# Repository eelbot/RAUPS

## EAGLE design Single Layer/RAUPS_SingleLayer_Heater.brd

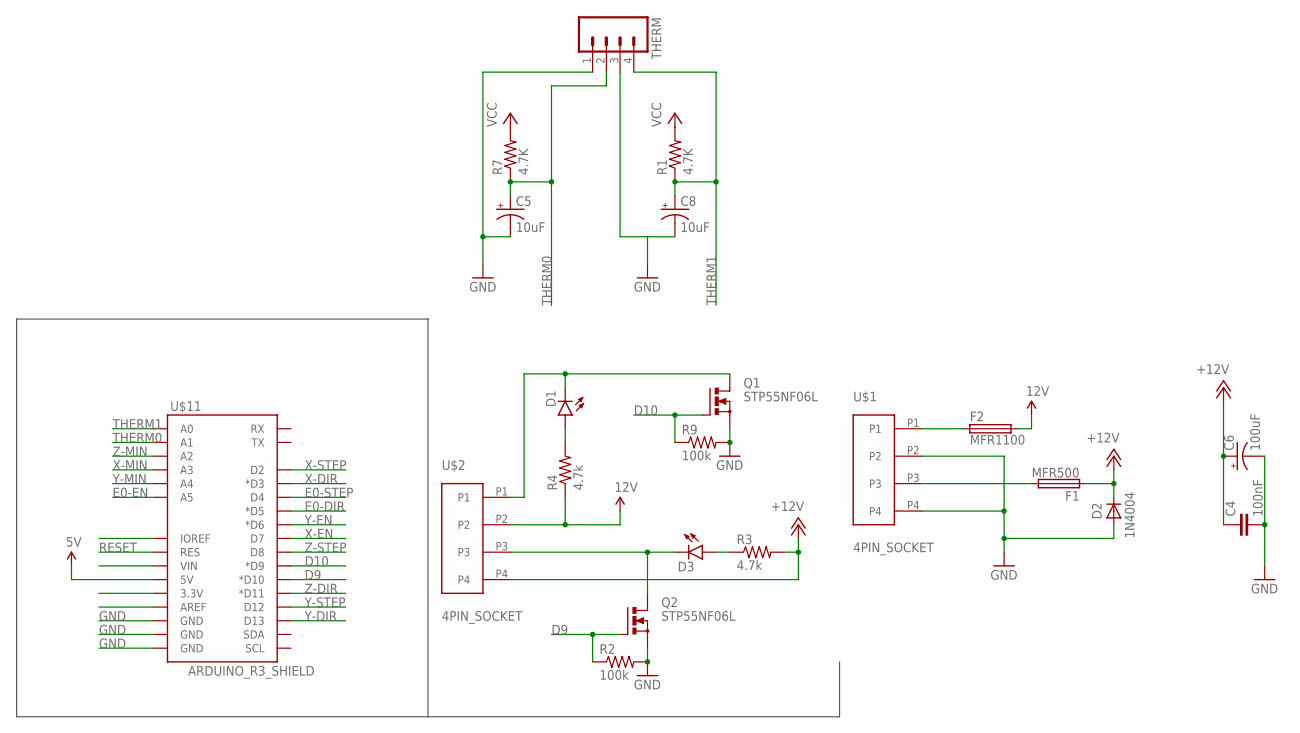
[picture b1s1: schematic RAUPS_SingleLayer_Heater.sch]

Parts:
C4: 100nF; C2.5-3
C5, C8: 10uF; E2,5-5
C6: 100uF; E3,5-8
D1, D3: LED-3MM-NO_SILK; LED3MM-NS
D2: 1N4004; DO41-10
F1: MFR500
F2: MFR1100
Q1, Q2: STP55NF06L; TO220BV
R1, R7: 4.7K; 0207/7
R2, R9: 100k; 0207/7
R3, R4: 4.7k; AXIAL-0.3
THERM: M04LONGPADS; 1X04_LONGPADS
U$1, U$2: 4PIN_SOCKET; CONN-4PIN
U$11: ARDUINO_R3_SHIELD; UNO_R3_SHIELD

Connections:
5V: U$11.5V
12V: F2.2, R4.P$1 (1), U$2.P2
+12V: C4.1, C6.+, D2.C, F1.1, R3.P$2 (2), U$2.P4
D9: Q2.G, R2.1, U$11.D10 (*D10)
D10: Q1.G, R9.1, U$11.D9 (*D9)
E0-DIR: U$11.D5 (*D5)
E0-EN: U$11.A5
E0-STEP: U$11.D4
GND: C4.2, C5.-, C6.-, C8.-, D2.A, Q1.S, Q2.S, R2.2, R9.2, THERM.1, THERM.3, U$1.P2, U$1.P4, U$11.GND@0 (GND), U$11.GND@1 (GND), U$11.GND@2 (GND)
unnamed: D3.K (C), Q2.D, U$2.P3
unnamed: F2.1, U$1.P1
unnamed: D1.K (C), Q1.D, U$2.P1
unnamed: F1.2, U$1.P3
unnamed: D1.A, R4.P$2 (2)
unnamed: D3.A, R3.P$1 (1)
RESET: U$11.RES
THERM0: C5.+, R7.1, THERM.2, U$11.A1
THERM1: C8.+, R1.1, THERM.4, U$11.A0
VCC: R1.2, R7.2
X-DIR: U$11.D3 (*D3)
X-EN: U$11.D7
X-MIN: U$11.A3
X-STEP: U$11.D2
Y-DIR: U$11.D13
Y-EN: U$11.D6 (*D6)
Y-MIN: U$11.A4
Y-STEP: U$11.D12
Z-DIR: U$11.D11 (*D11)
Z-MIN: U$11.A2
Z-STEP: U$11.D8

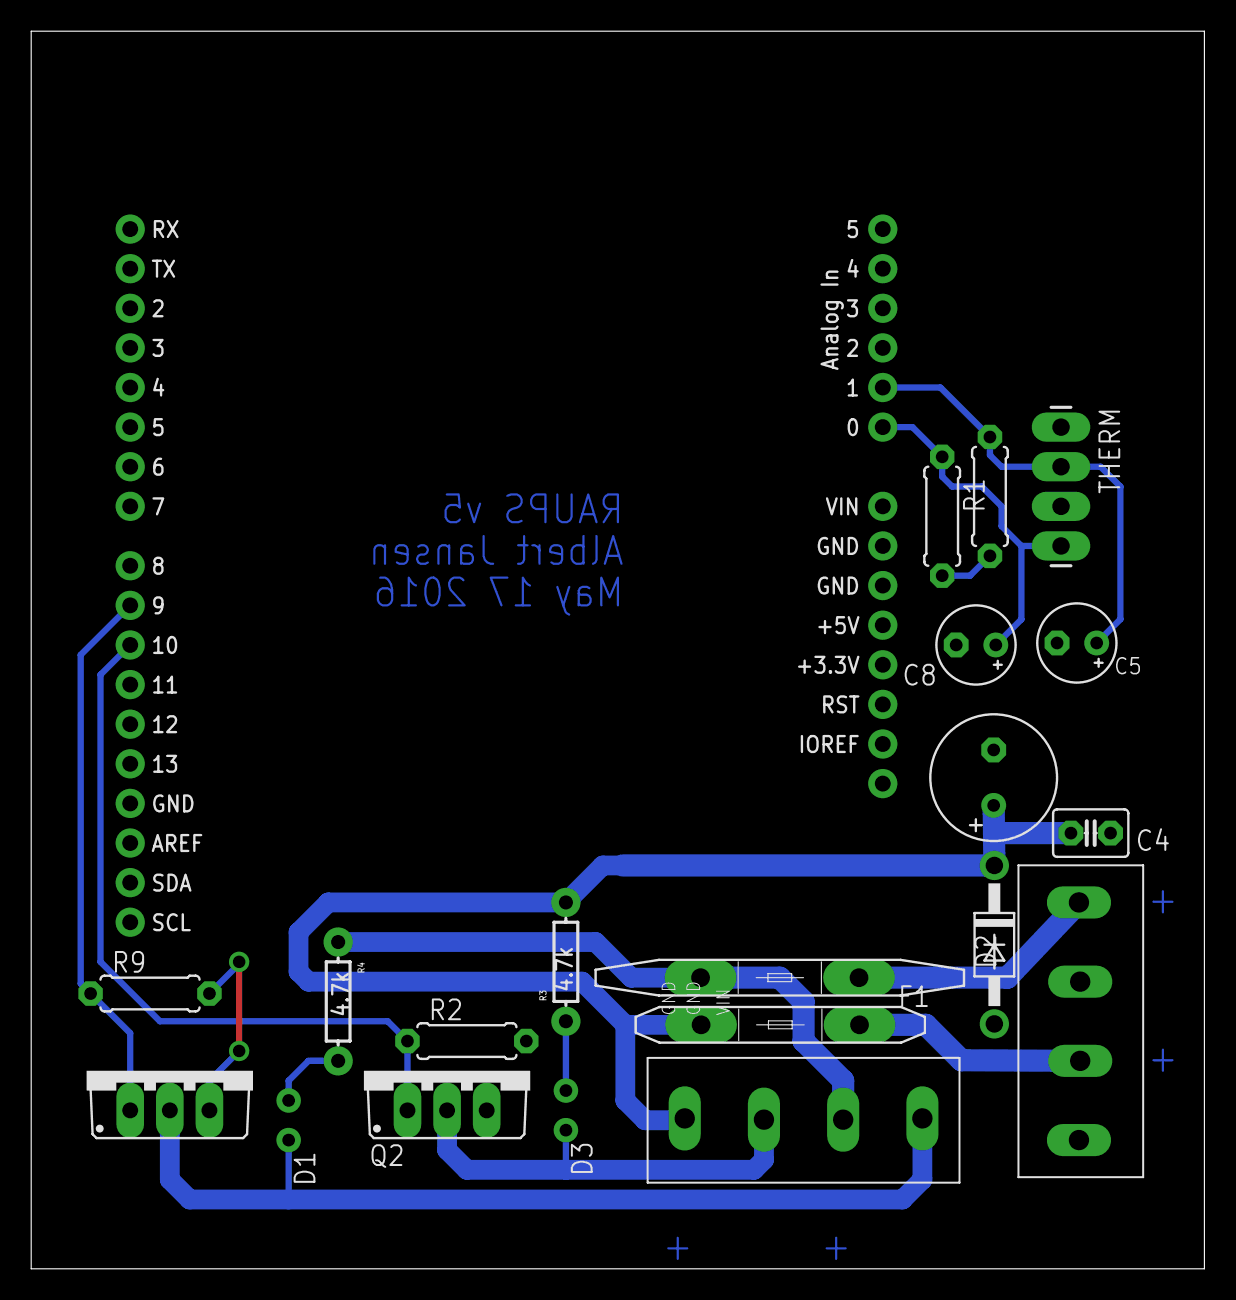
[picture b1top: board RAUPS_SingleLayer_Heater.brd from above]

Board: 2 copper layers, 75.2 x 79.4 mm, 21 parts (0 on the bottom side), 14 nets.

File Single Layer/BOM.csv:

Part Name,Package,Quantity,Digikey Part Number
Indicator LED,3mm,2,365-1173-ND
"1x3 0.1"" Header",PTH,3,3M9448-ND
"2x3 0.1"" Header",PTH,4,3M9459-ND
"1x4 0.1"" Header",PTH,6,3M9449-ND
"1x6 0.1"" Header",PTH,2,3M9451-ND
"1x8 0.1"" Header (Female)",PTH,8,S7041-ND
"1x8 0.1"" Header (Male)",PTH,4,3M9452-ND
"1x10 0.1"" Header",PTH,2,609-3250-ND
4.7k Resistor,PTH,2,S4.7KCACT-ND
10k Resistor,PTH,4,CF14JT10K0CT-ND
100k Resistor,PTH,6,CF14JT100KCT-ND
100nF Capacitor,PTH,2,445-5303-ND
100uF Capacitor,PTH,2,P5182-ND
10uF Capacitor,PTH,2,445-5339-ND
1N4004 Diode,PTH,2,1N4004FSCT-ND
"0.2"" Pitch Screw Terminal (2POS)",PTH,1,ED10561-ND
"0.2"" Pitch Screw Terminal (4POS)",PTH,1,ED10563-ND
PTC Resettable Fuse (11A),PTH,1,RGEF1100-ND
PTC Resettable Fuse (5A),PTH,2,MF-R500-ND
STP55NF06L MOSFET,PTH,2,497-6742-5-ND

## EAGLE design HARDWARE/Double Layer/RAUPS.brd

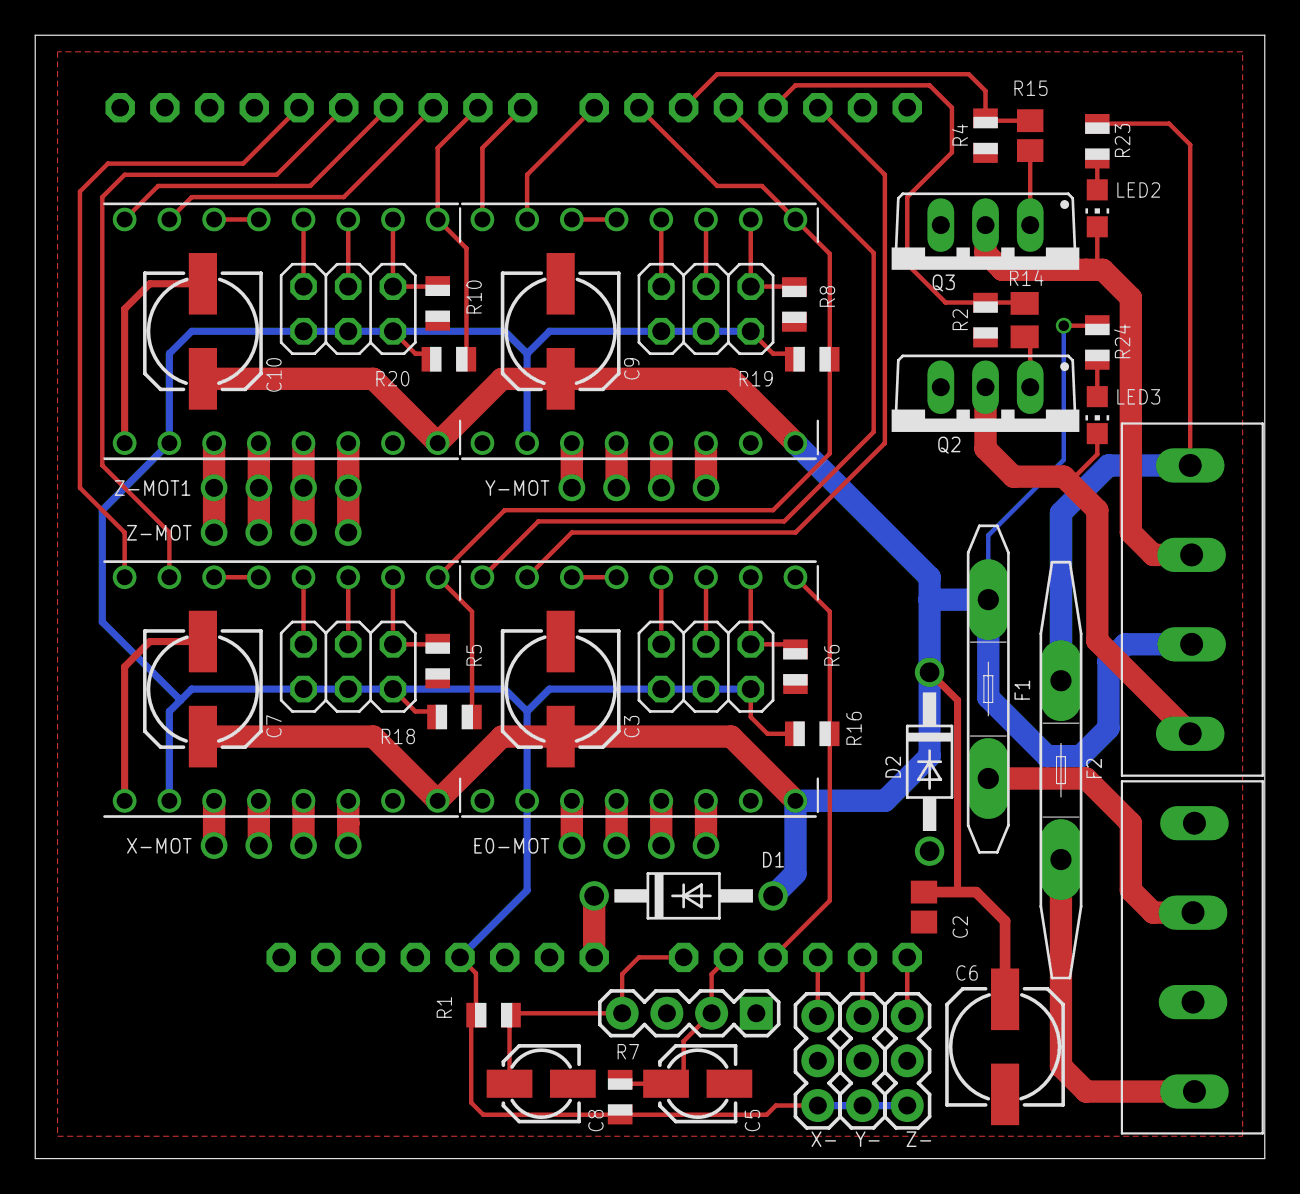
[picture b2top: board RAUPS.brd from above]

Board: 2 copper layers, 69.8 x 63.8 mm, 52 parts (0 on the bottom side), 63 nets.

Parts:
C2: 100nF; C0805
C3, C6, C7, C9, C10: 100uF; 153CLV-0605
C5, C8: 10uF; 153CLV-0405
D1, D2: 1N4004; DO41-10
E0-DRIVE: POLOLU_A4983CARRIER; A4988BREAKOUT
E0-MOT: 1X04
F1: MFR500
F2: MFR1100
JP1: 1X04
JP2, JP4, JP5, JP6: 2X03
LED2, LED3: CHIP-LED0805
Q2, Q3: STP55NF06L; TO220BV
R1, R7: 4.7K; R0805
R2, R4, R5, R6, R8, R10: 100k; R0805
R14: 10r; M0805
R15: 10r; R0805
R16, R18, R19, R20: 10k; R0805
R23, R24: 1.8K; R0805
U1: ARDUINOR3-BPLACE
U$1, U$2: 4PIN_SOCKET; CONN-4PIN
X-: 1X03
X-DRIVE: A4988BREAKOUT
X-MOT: 1X04
Y-: 1X03
Y-DRIVE: POLOLU_A4983CARRIER; A4988BREAKOUT
Y-MOT: 1X04
Z-: 1X03
Z-DRIVE: POLOLU_A4983CARRIER; A4988BREAKOUT
Z-MOT, Z-MOT1: 1X04

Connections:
+12V: C2.1, C3.+, C6.+, C7.+, C9.+, C10.+, D1.A, D2.C, E0-DRIVE.VMOT, F1.1, R24.1, U$2.P3, X-DRIVE.VMOT, Y-DRIVE.VMOT, Z-DRIVE.VMOT
+12V2: F2.2, R23.1, U$2.P1
D8: R4.1, R15.1, U1.D5
D9: R2.1, R14.1, U1.D3
E0-DIR: E0-DRIVE.DIR, U1.D4
E0-EN: E0-DRIVE.EN, R16.2, U1.A2
E0-STEP: E0-DRIVE.STEP, U1.D2
GND: C2.2, C3.-, C5.-, C6.-, C7.-, C8.-, C9.-, C10.-, D2.A, E0-DRIVE.GND, E0-DRIVE.GND@0, JP1.1, JP1.3, Q2.S, Q3.S, R2.2, R4.2, R5.2, R6.1, R8.2, R10.2, U1.GND, U1.GND1, U1.GND2, U$1.P2, U$1.P4, X-.2, X-DRIVE.GND, X-DRIVE.GND@0, Y-.2, Y-DRIVE.GND, Y-DRIVE.GND@0, Z-.2, Z-DRIVE.GND, Z-DRIVE.GND@0
unnamed: LED3.C, Q2.D, U$2.P4
unnamed: E0-DRIVE.2B, E0-MOT.1
unnamed: E0-DRIVE.2A, E0-MOT.2
unnamed: E0-DRIVE.MS1, JP2.1, R6.2
unnamed: E0-DRIVE.MS3, JP2.5
unnamed: E0-DRIVE.RST, E0-DRIVE.SLP
unnamed: E0-DRIVE.MS2, JP2.3
unnamed: E0-DRIVE.1A, E0-MOT.3
unnamed: E0-DRIVE.1B, E0-MOT.4
unnamed: JP4.1, R5.1, X-DRIVE.MS1
unnamed: JP4.3, X-DRIVE.MS2
unnamed: JP5.3, Y-DRIVE.MS2
unnamed: JP4.5, X-DRIVE.MS3
unnamed: X-DRIVE.RST, X-DRIVE.SLP
unnamed: X-DRIVE.2B, X-MOT.1
unnamed: X-DRIVE.2A, X-MOT.2
unnamed: Y-DRIVE.RST, Y-DRIVE.SLP
unnamed: X-DRIVE.1A, X-MOT.3
unnamed: X-DRIVE.1B, X-MOT.4
unnamed: Y-DRIVE.2B, Y-MOT.1
unnamed: Y-DRIVE.2A, Y-MOT.2
unnamed: Y-DRIVE.1A, Y-MOT.3
unnamed: JP5.5, Y-DRIVE.MS3
unnamed: LED2.A, R23.2
unnamed: JP5.1, R8.1, Y-DRIVE.MS1
unnamed: Y-DRIVE.1B, Y-MOT.4
unnamed: JP6.3, Z-DRIVE.MS2
unnamed: Z-DRIVE.RST, Z-DRIVE.SLP
unnamed: JP6.5, Z-DRIVE.MS3
unnamed: JP6.1, R10.1, Z-DRIVE.MS1
unnamed: Z-DRIVE.2B, Z-MOT.1, Z-MOT1.1
unnamed: Z-DRIVE.2A, Z-MOT.2, Z-MOT1.2
unnamed: Z-DRIVE.1A, Z-MOT.3, Z-MOT1.3
unnamed: Z-DRIVE.1B, Z-MOT.4, Z-MOT1.4
unnamed: LED3.A, R24.2
unnamed: Q2.G, R14.2
unnamed: Q3.G, R15.2
unnamed: LED2.C, Q3.D, U$2.P2
unnamed: F2.1, U$1.P1
unnamed: F1.2, U$1.P3
THERM0: C5.+, JP1.2, R7.1, U1.A1
THERM1: C8.+, JP1.4, R1.1, U1.A0
VCC: E0-DRIVE.VDD, JP2.2, JP2.4, JP2.6, JP4.2, JP4.4, JP4.6, JP5.2, JP5.4, JP5.6, JP6.2, JP6.4, JP6.6, R1.2, R7.2, R16.1, R18.1, R19.1, R20.1, U1.5V, X-.3, X-DRIVE.VDD, Y-.3, Y-DRIVE.VDD, Z-.3, Z-DRIVE.VDD
VIN: D1.C, U1.VIN
X-DIR: U1.D13, X-DRIVE.DIR
X-MIN: U1.A3, X-.1
X-STEP: U1.D12, X-DRIVE.STEP
Y-DIR: U1.D8, Y-DRIVE.DIR
Y-EN: R18.2, R19.2, U1.D6, X-DRIVE.EN, Y-DRIVE.EN
Y-MIN: U1.A4, Y-.1
Y-STEP: U1.D7, Y-DRIVE.STEP
Z-DIR: U1.D11, Z-DRIVE.DIR
Z-EN: R20.2, U1.D9, Z-DRIVE.EN
Z-MIN: U1.A5, Z-.1
Z-STEP: U1.D10, Z-DRIVE.STEP

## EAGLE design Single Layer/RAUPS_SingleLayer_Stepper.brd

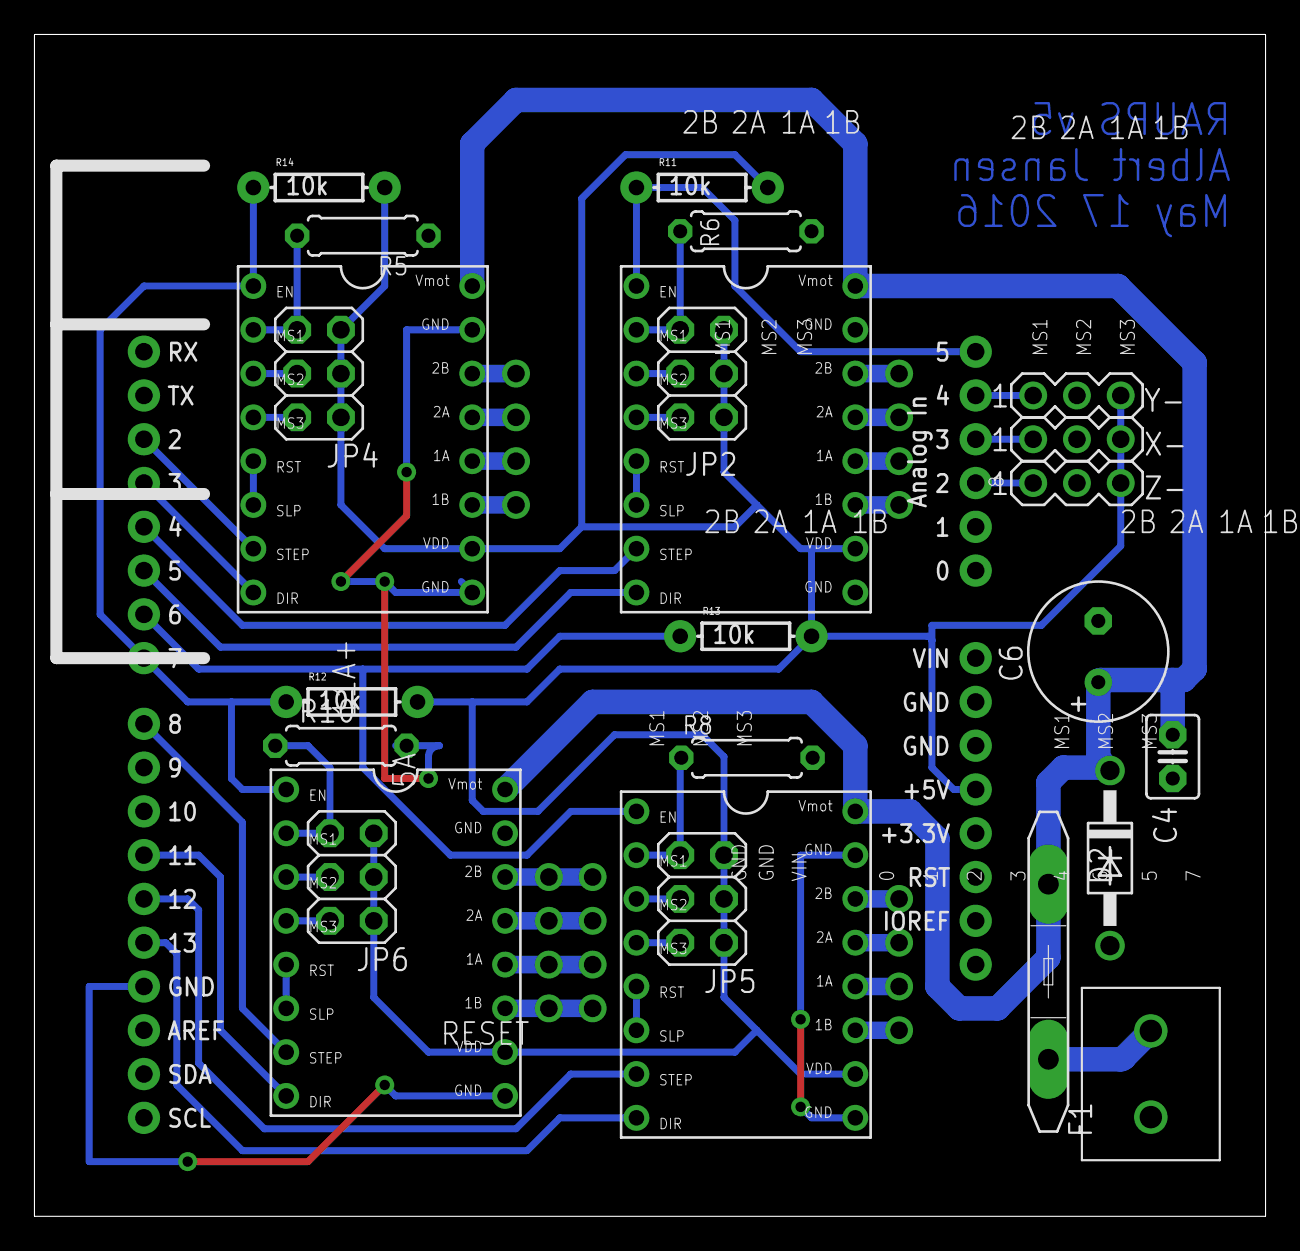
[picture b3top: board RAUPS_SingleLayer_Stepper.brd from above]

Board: 2 copper layers, 71.4 x 68.6 mm, 30 parts (0 on the bottom side), 50 nets.

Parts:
C4: 100nF; C2.5-3
C6: 470uF; E3,5-8
D2: 1N4004; DO41-10
E0-MOT: 1X04
F1: MFR500
JP2, JP4, JP5, JP6: 2X03
R5, R6, R8, R10: 100k; 0207/7
R11, R12, R13, R14: 10k; AXIAL-0.3
U$1: 2PIN_SOCKET; CONN-2PIN
U$4, U$6, U$7, U$8: A4988BREAKOUT
U$11: ARDUINO_R3_SHIELD; UNO_R3_SHIELD
X-: 3PIN-HEADER
X-MOT: 1X04
Y-: 3PIN-HEADER
Y-MOT: 1X04
Z-: 3PIN-HEADER
Z-MOT, Z-MOT1: 1X04

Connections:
+12V: C4.1, C6.+, D2.C, F1.1, U$4.VMOT, U$6.VMOT, U$7.VMOT, U$8.VMOT
E0-DIR: U$4.DIR, U$11.D5
E0-EN: R11.P$1, U$4.EN, U$11.A5
E0-STEP: U$4.STEP, U$11.D4
GND: C4.2, C6.-, D2.A, R5.2, R6.1, R8.2, R10.2, U$1.P$2, U$4.GND, U$4.GND@0, U$6.GND, U$6.GND@0, U$7.GND, U$7.GND@0, U$8.GND, U$8.GND@0, U$11.GND@0, U$11.GND@1, U$11.GND@2, X-.2, Y-.2, Z-.2
unnamed: E0-MOT.1, U$4.2B
unnamed: E0-MOT.2, U$4.2A
unnamed: JP2.1, R6.2, U$4.MS1
unnamed: JP2.5, U$4.MS3
unnamed: U$4.RST, U$4.SLP
unnamed: JP2.3, U$4.MS2
unnamed: E0-MOT.3, U$4.1A
unnamed: E0-MOT.4, U$4.1B
unnamed: JP4.1, R5.1, U$6.MS1
unnamed: JP4.3, U$6.MS2
unnamed: JP5.3, U$7.MS2
unnamed: JP4.5, U$6.MS3
unnamed: U$6.RST, U$6.SLP
unnamed: U$6.2B, X-MOT.1
unnamed: U$6.2A, X-MOT.2
unnamed: U$7.RST, U$7.SLP
unnamed: U$6.1A, X-MOT.3
unnamed: U$6.1B, X-MOT.4
unnamed: U$7.2B, Y-MOT.1
unnamed: U$7.2A, Y-MOT.2
unnamed: U$7.1A, Y-MOT.3
unnamed: JP5.5, U$7.MS3
unnamed: F1.2, U$1.P$1
unnamed: JP5.1, R8.1, U$7.MS1
unnamed: U$7.1B, Y-MOT.4
unnamed: JP6.3, U$8.MS2
unnamed: U$8.RST, U$8.SLP
unnamed: JP6.5, U$8.MS3
unnamed: JP6.1, R10.1, U$8.MS1
unnamed: U$8.2B, Z-MOT.1, Z-MOT1.1
unnamed: U$8.2A, Z-MOT.2, Z-MOT1.2
unnamed: U$8.1A, Z-MOT.3, Z-MOT1.3
unnamed: U$8.1B, Z-MOT.4, Z-MOT1.4
VCC: JP2.2, JP2.4, JP2.6, JP4.2, JP4.4, JP4.6, JP5.2, JP5.4, JP5.6, JP6.2, JP6.4, JP6.6, R11.P$2, R12.P$2, R13.P$2, R14.P$2, U$4.VDD, U$6.VDD, U$7.VDD, U$8.VDD, U$11.5V, X-.3, Y-.3, Z-.3
X-DIR: U$6.DIR, U$11.D3
X-EN: R12.P$1, R14.P$1, U$6.EN, U$8.EN, U$11.D7
X-MIN: U$11.A3, X-.1
X-STEP: U$6.STEP, U$11.D2
Y-DIR: U$7.DIR, U$11.D13
Y-EN: R13.P$1, U$7.EN, U$11.D6
Y-MIN: U$11.A4, Y-.1
Y-STEP: U$7.STEP, U$11.D12
Z-DIR: U$8.DIR, U$11.D11
Z-MIN: U$11.A2, Z-.1
Z-STEP: U$8.STEP, U$11.D8

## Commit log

2016-05-13 Creation of new repository to better reflect the contents of RAUPS
2016-05-13 Began work on 2 layer version of RAUPS
2016-05-14 Finished routing of 2 layer board, DRC complete
2016-05-17 Added BOM, final single layer board tweaks, and re-organized file structure to better reflect project goals
2016-05-18 Changed screw terminal part numbers

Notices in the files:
parts and their libraries:
SparkFun-Connectors: Licensing: Creative Commons ShareAlike 4.0 International - https://creativecommons.org/licenses/by-sa/4.0
